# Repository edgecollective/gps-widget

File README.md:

# gps-widget

cam m8 q breakout waterott [https://github.com/watterott/CAM-M8Q-Breakout/tree/master/hardware](https://github.com/watterott/CAM-M8Q-Breakout/tree/master/hardware)

adafruit breakout pcbs [https://github.com/adafruit/Adafruit-E-Paper-Display-Breakout-PCBs](https://github.com/adafruit/Adafruit-E-Paper-Display-Breakout-PCBs)

schematic review for epaper display [https://www.reddit.com/r/PrintedCircuitBoard/comments/dayjnn/schematic_review_for_esp32_and_epaper_display/]

technoblogy 1284p [post](http://www.technoblogy.com/show?19OV)

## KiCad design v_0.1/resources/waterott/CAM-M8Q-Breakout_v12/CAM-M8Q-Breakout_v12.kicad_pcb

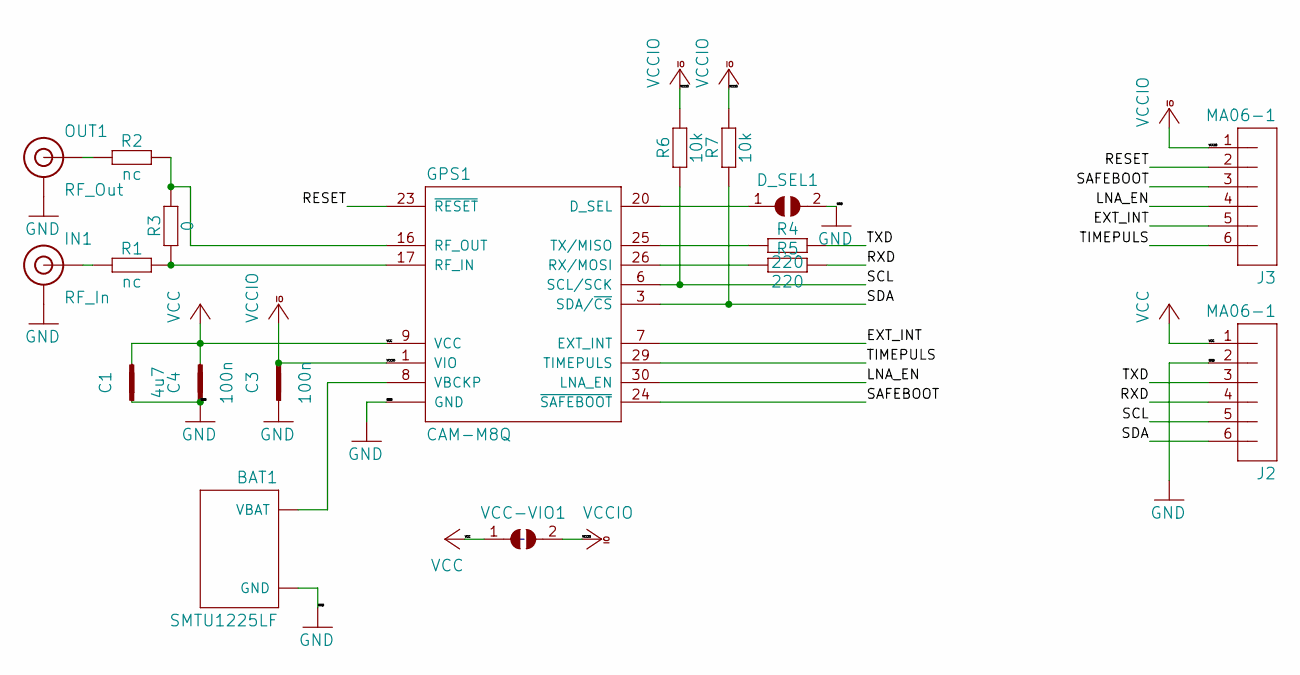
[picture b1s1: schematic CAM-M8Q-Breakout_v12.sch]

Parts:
BAT1: SMTU1225LF; BAT-SMTU1225LF
C1: 4u7; C0402
C3, C4: 100n; C0402
D_SEL1: JUMPER2-0603-NC; JUMPER2-0603_NC
GPS1: CAM-M8Q
IN1: RF_In; U.FL
J2, J3: MA06-1
OUT1: RF_Out; U.FL
R1, R2: nc; C0402
R3: 0; C0402
R4, R5: 220; C0402
R6, R7: 10k; C0402
VCC-VIO1: JUMPER2-0603-NC; JUMPER2-0603_NC

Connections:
/EXT_INT: GPS1.7 (EXT_INT), J3.5
/LNA_EN: GPS1.30 (LNA_EN), J3.4
/RESET: GPS1.23 (~RESET), J3.2
/RXD: J2.4, R5.2
/SAFEBOOT: GPS1.24 (~SAFEBOOT), J3.3
/SCL: GPS1.6 (SCL/SCK), J2.5, R6.1
/SDA: GPS1.3 (SDA/~CS), J2.6, R7.1
/TIMEPULS: GPS1.29 (TIMEPULS), J3.6
/TXD: J2.3, R4.2
GND: BAT1.- (GND), C1.1, C3.1, C4.1, D_SEL1.2, GPS1.4 (GND), GPS1.5 (GND), GPS1.10 (GND), GPS1.11 (GND), GPS1.12 (GND), GPS1.13 (GND), GPS1.14 (GND), GPS1.15 (GND), GPS1.18 (GND), GPS1.19 (GND), GPS1.21 (GND), GPS1.22 (GND), GPS1.27 (GND), GPS1.31 (GND), IN1.1 (GND), IN1.2 (GND), J2.2, OUT1.1 (GND), OUT1.2 (GND)
unnamed: BAT1.+ (VBAT), GPS1.8 (VBCKP)
unnamed: D_SEL1.1, GPS1.20 (D_SEL)
unnamed: GPS1.16 (RF_OUT), R2.2, R3.2
unnamed: GPS1.17 (RF_IN), R1.2, R3.1
unnamed: GPS1.25 (TX/MISO), R4.1
unnamed: GPS1.26 (RX/MOSI), R5.1
unnamed: IN1.FEED (SIGNAL), R1.1
unnamed: OUT1.FEED (SIGNAL), R2.1
VCC: C1.2, C4.2, GPS1.9 (VCC), J2.1, VCC-VIO1.1
VCCIO: C3.2, GPS1.1 (VIO), J3.1, R6.2, R7.2, VCC-VIO1.2

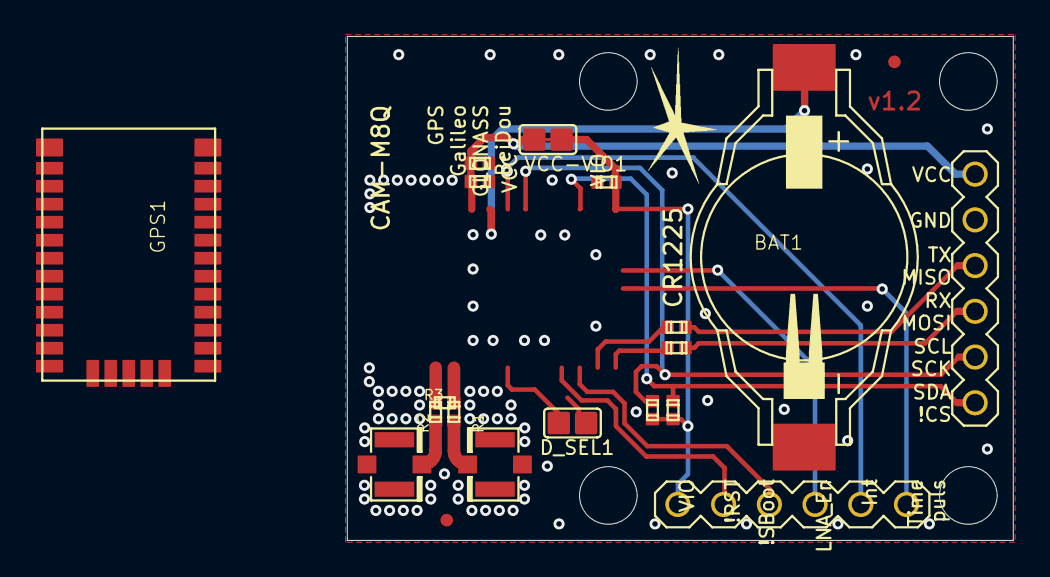
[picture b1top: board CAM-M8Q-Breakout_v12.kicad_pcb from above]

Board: 2 copper layers, 37.0 x 28.0 mm, 31 parts (0 on the bottom side), 20 nets.

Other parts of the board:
@HOLE0, @HOLE1, @HOLE2, @HOLE3: (no value)
LOGO1: LOGO-S_PLACE_M; SPARK_TPLACE_M
LOGO2: OSHW_LOGOX0070; OSHW_6X70
LOGO3: LOGO_CE-2; CE_2MM
LOGO4: LOGO_WEEE-4; WEEE_4MM
LOGO5: LOGO_ROHS-2; ROHS_2MM
X1, X2, X3, X4: PASSER-07; PASSER_07MM

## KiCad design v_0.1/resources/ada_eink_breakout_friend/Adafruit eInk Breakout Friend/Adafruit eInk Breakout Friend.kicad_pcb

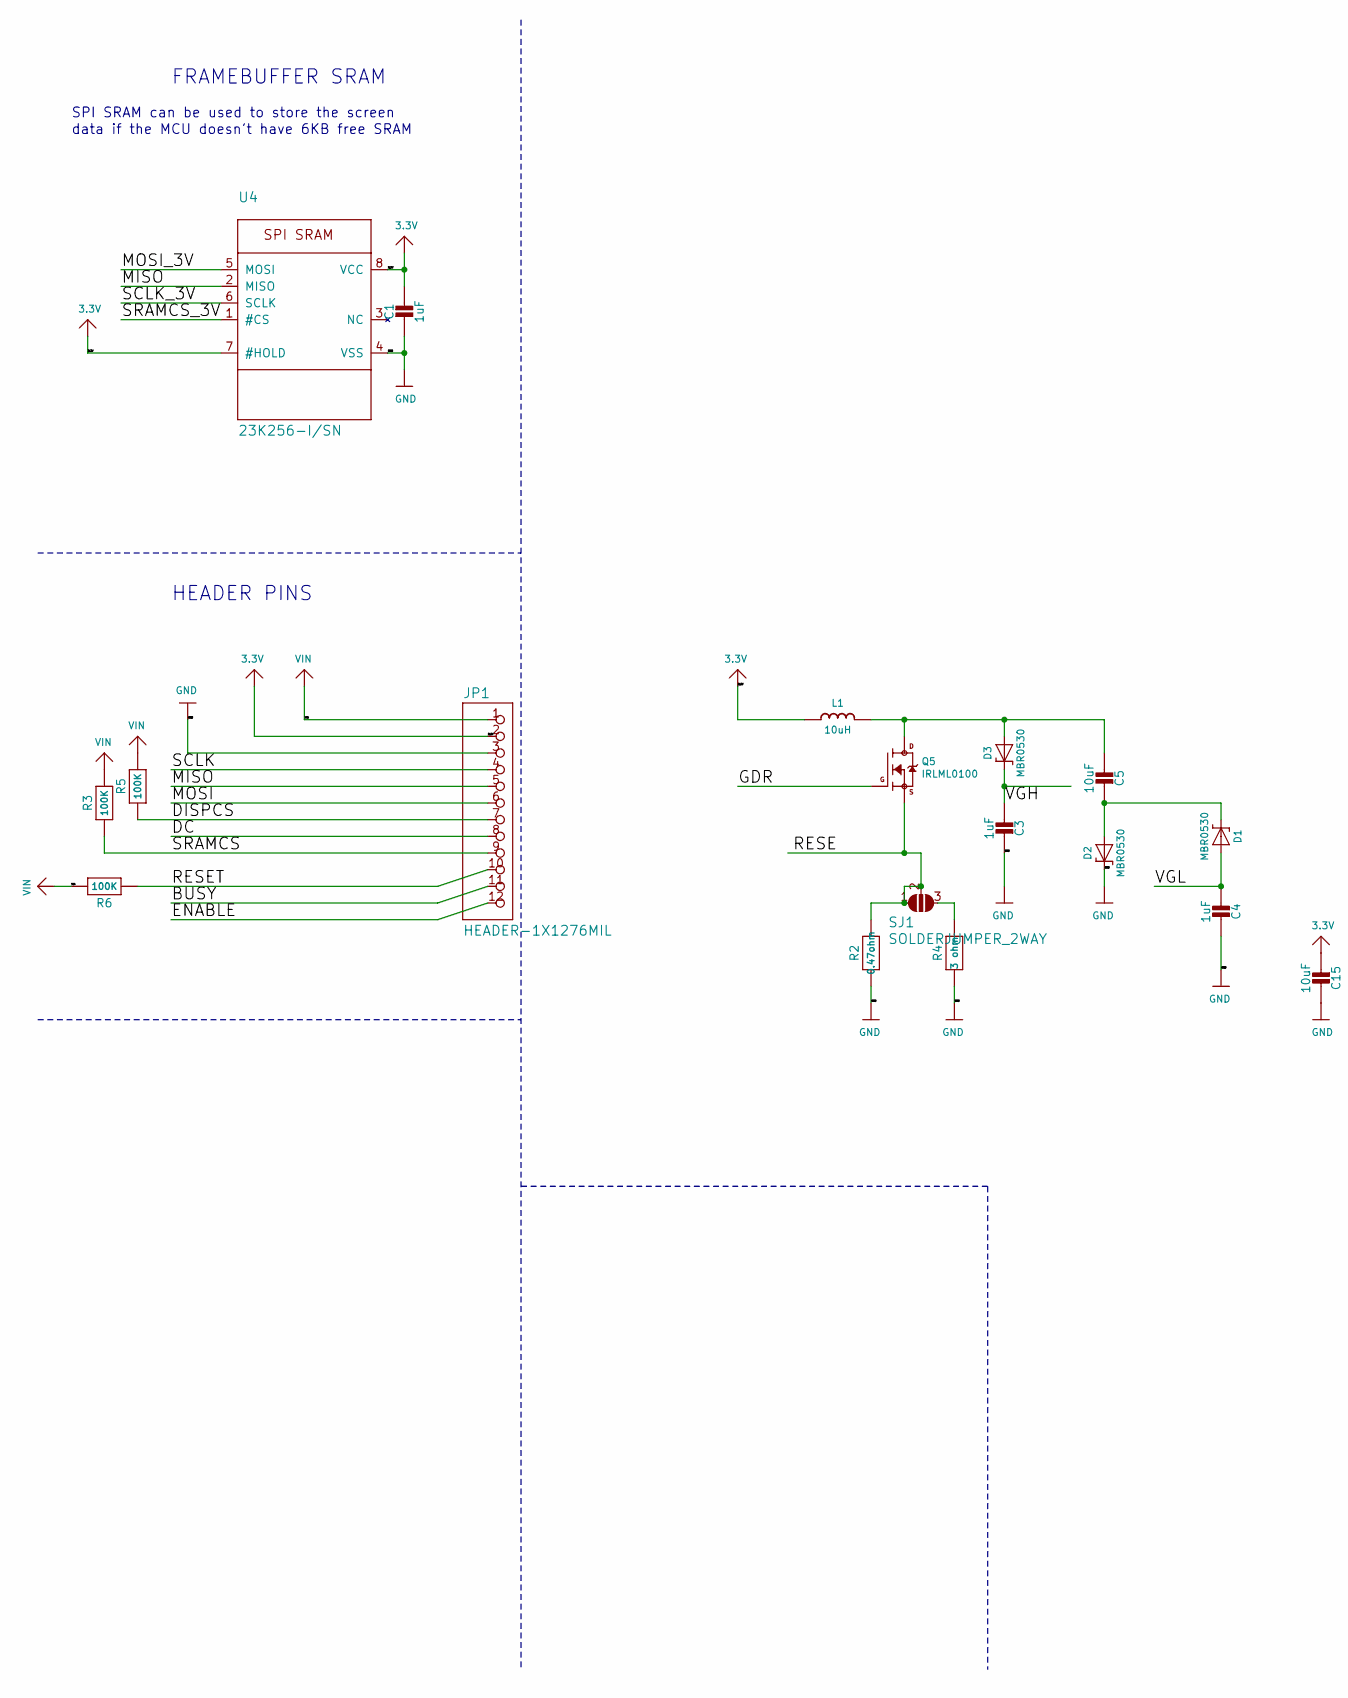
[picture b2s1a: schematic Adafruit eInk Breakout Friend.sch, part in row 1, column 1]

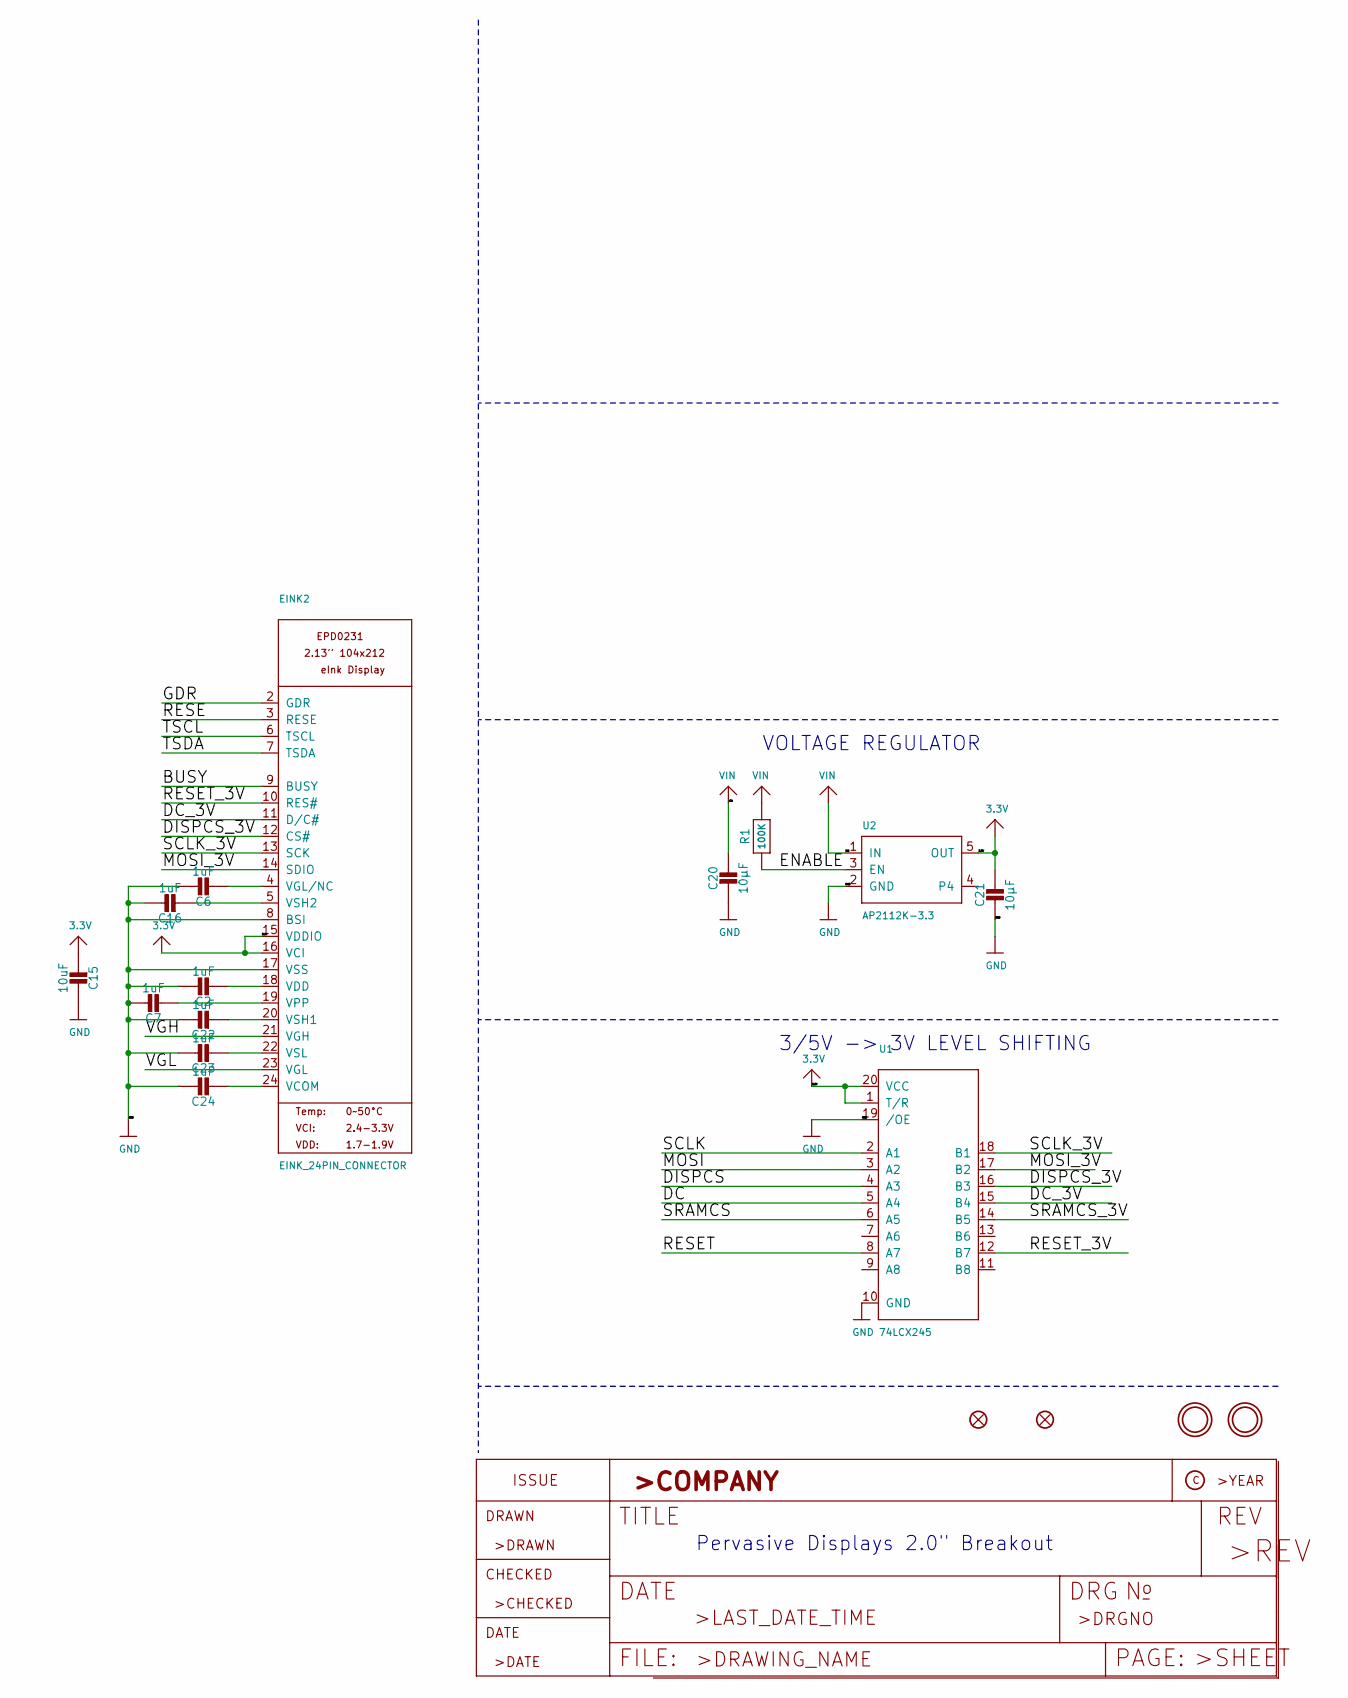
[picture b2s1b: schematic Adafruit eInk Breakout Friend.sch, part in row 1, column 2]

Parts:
C1: 1uF; 0805_10MGAP
C2, C3, C4, C6, C7, C16, C22, C23, C24: 1uF; 0805-NO
C5, C15: 10uF; 0805-NO
C20, C21: 10µF; 0805-NO
D1, D2, D3: MBR0530; SOD-123
EINK2: EINK_24PIN_CONNECTOR; EINK_24PIN
FID2, FID3: FIDUCIAL_1MM
JP1: HEADER-1X1276MIL; 1X12_ROUND_76MIL
L1: 10uH; INDUCTOR_4X4MM_NR401
Q5: IRLML0100; SOT23-3
R1, R3, R5, R6: 100K; 0603-NO
R2: 0.47ohm; 0805-NO
R4: 3 ohm; 0805-NO
SJ1: SOLDERJUMPER_2WAY; SOLDERJUMPER_2WAY_OPEN_NOPASTE
U1: 74LCX245; TSSOP20
U2: AP2112K-3.3; SOT23-5
U4: 23K256-I/SN; SOIC8_150MIL
U$3, U$4: MOUNTINGHOLE2.5; MOUNTINGHOLE_2.5_PLATED

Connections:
3.3V: C1.1, C15.2, C21.1, EINK2.15 (VDDIO), EINK2.16 (VCI), JP1.2, L1.P$2 (2), U1.1 (T/R), U1.20 (VCC), U2.5 (OUT), U4.7 (#HOLD), U4.8 (VCC)
/BUSY: EINK2.9 (BUSY), JP1.11
/DC: JP1.8, U1.5 (A4)
/DC_3V: EINK2.11 (D/C#), U1.15 (B4)
/DISPCS: JP1.7, R5.1, U1.4 (A3)
/DISPCS_3V: EINK2.12 (CS#), U1.16 (B3)
/ENABLE: JP1.12, R1.1, U2.3 (EN)
/GDR: EINK2.2 (GDR), Q5.1 (G)
/MISO: JP1.5, U4.2 (MISO)
/MOSI: JP1.6, U1.3 (A2)
/MOSI_3V: EINK2.14 (SDIO), U1.17 (B2), U4.5 (MOSI)
/RESE: EINK2.3 (RESE), Q5.2 (S), R2.1, SJ1.1, SJ1.2
/RESET: JP1.10, R6.1, U1.8 (A7)
/RESET_3V: EINK2.10 (RES#), U1.12 (B7)
/SCLK: JP1.4, U1.2 (A1)
/SCLK_3V: EINK2.13 (SCK), U1.18 (B1), U4.6 (SCLK)
/SRAMCS: JP1.9, R3.1, U1.6 (A5)
/SRAMCS_3V: U1.14 (B5), U4.1 (#CS)
/TSCL: EINK2.6 (TSCL)
/TSDA: EINK2.7 (TSDA)
/VGH: C3.1, D3.C, EINK2.21 (VGH)
/VGL: C4.1, D1.A, EINK2.23 (VGL)
GND: C1.2, C2.1, C3.2, C4.2, C6.1, C7.1, C15.1, C16.1, C20.2, C21.2, C22.1, C23.1, C24.1, D2.C, EINK2.8 (BSI), EINK2.17 (VSS), JP1.3, R2.2, R4.2, U1.10 (GND), U1.19 (/OE), U2.2 (GND), U4.4 (VSS)
unnamed: C2.2, EINK2.18 (VDD)
unnamed: C5.1, D3.A, L1.P$1 (1), Q5.3 (D)
unnamed: C5.2, D1.C, D2.A
unnamed: C6.2, EINK2.4 (VGL/NC)
unnamed: C7.2, EINK2.19 (VPP)
unnamed: C16.2, EINK2.5 (VSH2)
unnamed: C22.2, EINK2.20 (VSH1)
unnamed: C23.2, EINK2.22 (VSL)
unnamed: C24.2, EINK2.24 (VCOM)
unnamed: R4.1, SJ1.3
VIN: C20.1, JP1.1, R1.2, R3.2, R5.2, R6.2, U2.1 (IN)

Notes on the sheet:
Pervasive Displays 2.0" Breakout
VOLTAGE REGULATOR
3/5V -> 3V LEVEL SHIFTING
HEADER PINS
FRAMEBUFFER SRAM
SPI SRAM can be used to store the screen
data if the MCU doesn't have 6KB free SRAM

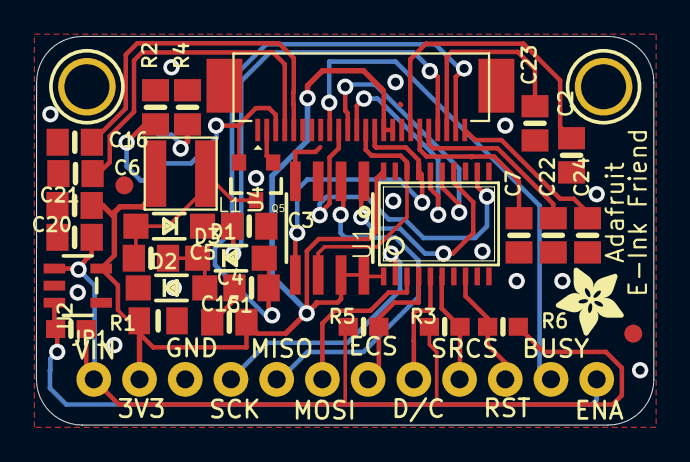
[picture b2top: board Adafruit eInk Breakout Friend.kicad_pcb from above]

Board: 2 copper layers, 34.3 x 21.6 mm, 37 parts (0 on the bottom side), 32 nets.

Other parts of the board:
U$2: ADAFRUIT_3.5MM
U$9: PCBFEAT-REV-040

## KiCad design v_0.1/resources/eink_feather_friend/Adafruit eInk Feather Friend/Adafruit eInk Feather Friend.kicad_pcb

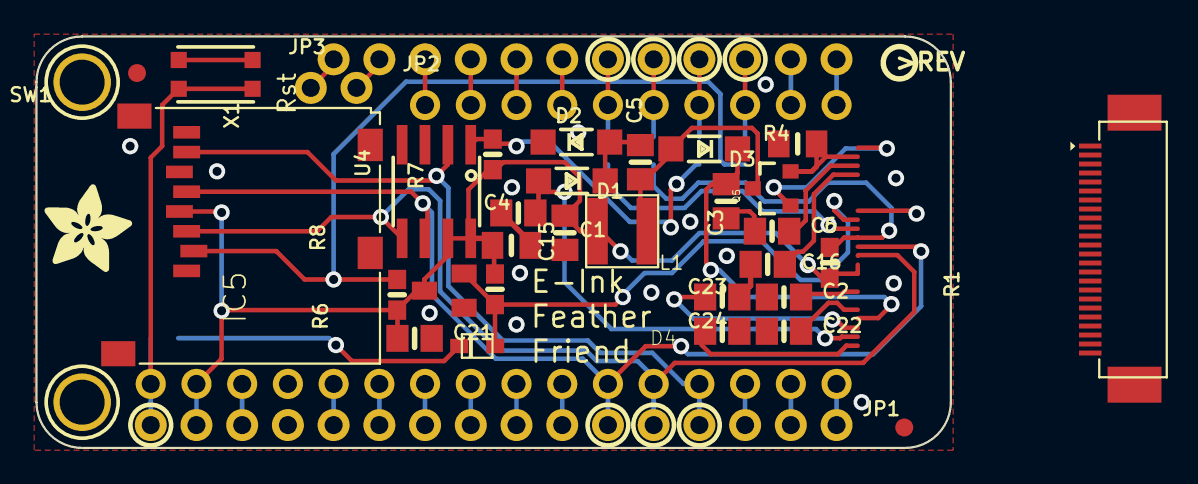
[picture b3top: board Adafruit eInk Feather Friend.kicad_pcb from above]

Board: 2 copper layers, 50.8 x 22.9 mm, 47 parts (0 on the bottom side), 47 nets.

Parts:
BUSY1: TPTP15SQ; TP15SQ
C1: 1uF; 0805_10MGAP
C2, C6: 1uF/10V; 0805-NO
C3, C4, C22, C23: 1uF/25V; 0805-NO
C5: 10uF/25V; 0805-NO
C15: 10uF/10V+; 0805-NO
C16, C24: 1uF; 0805-NO
C21: 10µF; 0805-NO
D1, D2, D3: MBR0530; SOD-123
D4: 1N4148; SOD-323F
EINK1: EINK_24PIN_CONNECTOR; EINK_24PIN
FID1, FID3: FIDUCIAL_1MM
IC5: AXP803; SOT23
JP1: HEADER-1X16ROUND; 1X16_ROUND
JP2: HEADER-1X10ROUND; 1X10_ROUND
JP3: HEADER-1X2ROUND; 1X02_ROUND
L1: 10uH; INDUCTOR_4X4MM_NR401
MS1: FEATHERWING_NOHOLES
Q5: IRLML0100; SOT23-3
R1, R6, R7, R8: 100K; 0603-NO
R4: .47ohm; 0805_10MGAP
SJ1, SJ2, SJ3, SJ4, SJ5: SOLDERJUMPER_CLOSED; SOLDERJUMPER_CLOSEDWIRE
SW1: 6mm SMT; BTN_KMR2_4.6X2.8
U4: 23K256-I/SN; SOIC8_150MIL
U$3, U$4: MOUNTINGHOLE2.5; MOUNTINGHOLE_2.5_PLATED
U$5: THINKINK_1.25IN
U$6: FEATHERLOGO_MED
U$8: ADAFRUIT_5MM
U$9: PCBFEAT-REV-040
U$17: ADAFRUIT_3.5MM
X1: MICROSD

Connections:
3.3V: C1.1, C15.2, C21.1, EINK1.15, EINK1.16, IC5.3, JP1.15, L1.P$2, MS1.2, R1.2, R6.2, R7.2, R8.2, U4.7, U4.8, X1.4
/BUSY: BUSY1.TP, EINK1.9
/DC: EINK1.11, SJ4.2
/EINK_CS: EINK1.12, R1.1, SJ1.2
/EINK_RESET: D4.A, EINK1.10, IC5.2, R8.1
/GDR: EINK1.2, Q5.1
/MISO: JP1.4, MS1.13, U4.2, X1.7
/MOSI: EINK1.14, JP1.5, MS1.12, U4.5, X1.3
/RESE: EINK1.3, Q5.2, R4.1
/RESET: JP1.16, MS1.1, SJ5.2, SW1.B, SW1.B'
/SCLK: EINK1.13, JP1.6, MS1.11, U4.6, X1.5
/SD_CS: R6.1, SJ3.2, X1.2
/SRAM_CS: R7.1, SJ2.2, U4.1
/VGH: C3.1, D3.C, EINK1.21
/VGL: C4.1, D1.A, EINK1.23
GND: C1.2, C2.1, C3.2, C4.2, C6.1, C15.1, C16.1, C21.2, C22.1, C23.1, C24.1, D2.C, EINK1.8, EINK1.17, IC5.1, JP1.13, MS1.4, R4.2, SW1.A, SW1.A', U4.4, X1.6, X1.MT1, X1.MT2
unnamed: C2.2, EINK1.18
unnamed: C5.1, D3.A, L1.P$1, Q5.3
unnamed: C5.2, D1.C, D2.A
unnamed: C6.2, EINK1.4
unnamed: C16.2, EINK1.5
unnamed: C22.2, EINK1.20
unnamed: C23.2, EINK1.22
unnamed: C24.2, EINK1.24
unnamed: D4.C, SJ5.1
unnamed: JP1.1, MS1.16
unnamed: JP1.2, MS1.15
unnamed: JP1.3, MS1.14
unnamed: JP1.7, MS1.10
unnamed: JP1.8, MS1.9
unnamed: JP1.9, MS1.8
unnamed: JP1.10, MS1.7
unnamed: JP1.11, MS1.6
unnamed: JP1.12, MS1.5
unnamed: JP1.14, MS1.3
unnamed: JP2.1, MS1.26
unnamed: JP2.2, MS1.25
unnamed: JP2.3, MS1.24
unnamed: JP2.4, MS1.23
unnamed: JP2.5, MS1.22, SJ4.1
unnamed: JP2.6, MS1.21, SJ1.1
unnamed: JP2.7, MS1.20, SJ2.1
unnamed: JP2.8, MS1.19, SJ3.1
unnamed: JP2.9, MS1.18
unnamed: JP2.10, MS1.17
unnamed: JP3.1, MS1.28
unnamed: JP3.2, MS1.27

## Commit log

2021-03-28 adding working proto
2021-03-28 adding working proto w gps
2021-03-28 adding working proto w sleep
2021-03-28 added image of working pin setup
2021-03-28 working with some bootup time ... to keep sd card happy
2021-03-29 added final pinout
2021-03-29 mighty_eink_transmit_sd_gps_sleep_exp1C_working sleeps at 0.1 mA
